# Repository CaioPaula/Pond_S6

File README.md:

# Atividade Semana 6

## Estrutura de pastas

    |--Gerber/
    |--Pond_S6-backups/
    |--Pond_S6.pretty/
    |--Pond_S6.kicad_pcb
    |--Pond_S6.kicad_sch
    |--Pond_S6.kicad_pro
    |--README.md

- A pasta "Gerber/" contém os arquivos Gerber gerados pelo KiCad. A pasta "
- O arquivo "Pond_S6.kicad_pcb" é o arquivo de placa do projeto KiCad.
- O arquivo "Pond_S6.kicad_sch" é o arquivo de esquema do projeto KiCad.
- O arquivo "Pond_S6.kicad_pro" é o arquivo de projeto do projeto KiCad.
- O arquivo "README.md" é este arquivo.

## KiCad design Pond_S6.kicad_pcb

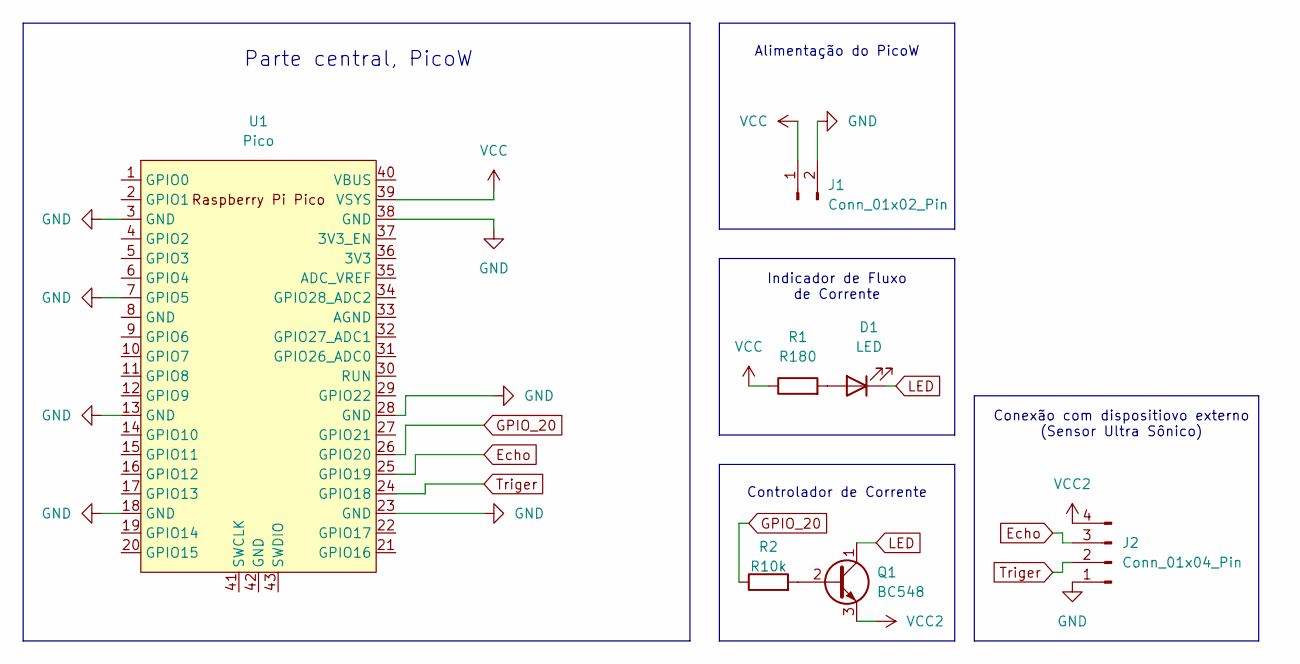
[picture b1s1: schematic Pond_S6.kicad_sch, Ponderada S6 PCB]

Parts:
D1: LED; LED_D5.0mm_Clear
J1: Conn_01x02_Pin; PinHeader_1x02_P1.27mm_Vertical
J2: Conn_01x04_Pin; PinHeader_1x04_P1.27mm_Vertical
Q1: BC548; TO-92_Inline
R1: R180; R_Axial_DIN0204_L3.6mm_D1.6mm_P5.08mm_Horizontal
R2: R10k; R_Axial_DIN0204_L3.6mm_D1.6mm_P5.08mm_Horizontal
U1: Pico; RPi_Pico_SMD_TH

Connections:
Echo: J2.3, U1.25 (GPIO19)
GND: J1.2, J2.1, U1.3 (GND), U1.7 (GPIO5), U1.13 (GND), U1.18 (GND), U1.23 (GND), U1.28 (GND), U1.38 (GND)
GPIO_20: R2.1, U1.26 (GPIO20)
LED: D1.1 (K), Q1.1 (C)
unnamed: D1.2 (A), R1.2
unnamed: Q1.2 (B), R2.2
Triger: J2.2, U1.24 (GPIO18)
VCC: J1.1, R1.1, U1.39 (VSYS)
VCC2: J2.4, Q1.3 (E)

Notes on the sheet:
Indicador de Fluxo de Corrente
Alimentação do PicoW
Conexão com dispositiovo externo (Sensor Ultra Sônico)
Controlador de Corrente
Parte central, PicoW

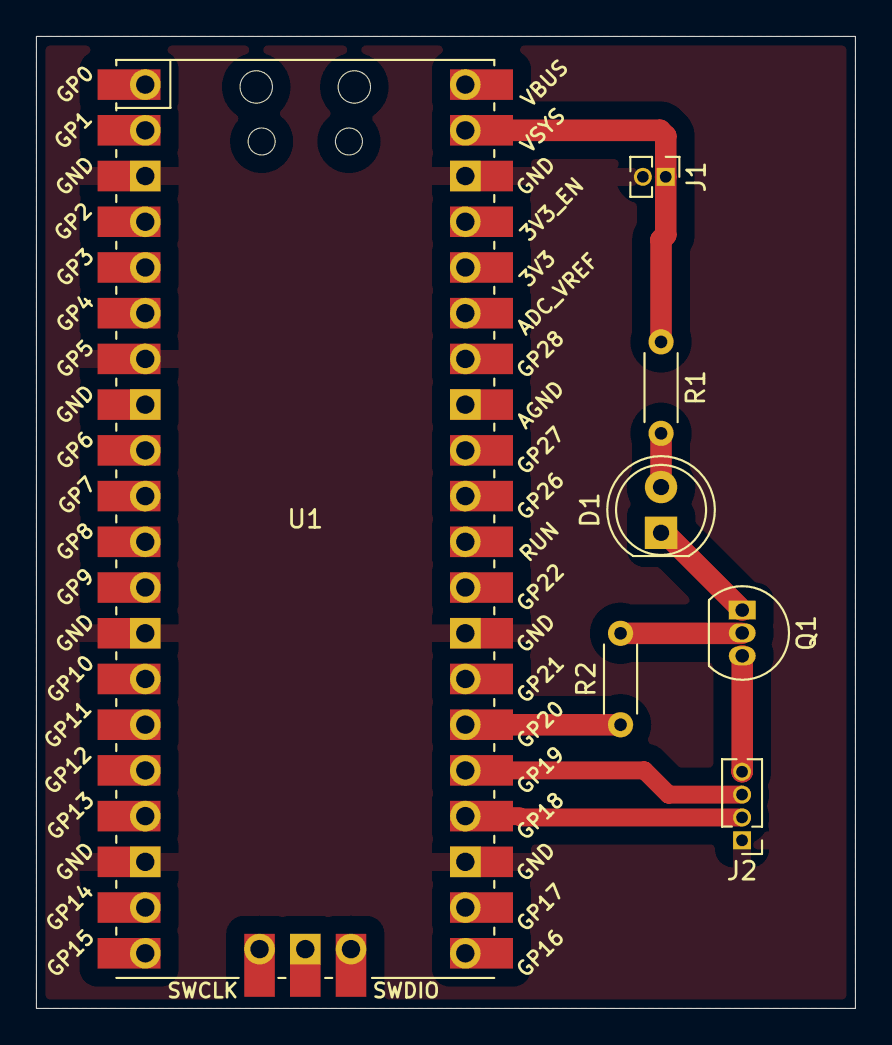
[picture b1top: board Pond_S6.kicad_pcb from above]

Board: 2 copper layers, 45.5 x 54.0 mm, 7 parts (0 on the bottom side), 9 nets.

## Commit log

2024-03-30 Ponderada semana 6
2024-03-30 Revert "Ponderada semana 6"
    This reverts commit 37a06c71d9f026bc5de133f22294cdac9d0ba8cd.
2024-03-30 Correção arquivos
2024-03-30 README e .gitignore
2024-03-30 Correções
